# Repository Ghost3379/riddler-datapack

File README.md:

# Enigma Data Pack - Robin: Origins

A functional custom electronic prop for the indie fan film *"Robin: Origins"*. The design is based on the iconic Enigma Data Packs from the Batman *Arkham* universe, engineered as an interactive gadget that can be carried on set and connected to a PC via USB-C to mount as an encrypted data drive.

---

## Hardware Versions

The project contains two distinct hardware designs:

1. **Mini Version (Movie Prop - In Production):** An ultra-compact, stunt-safe, pocket-sized tactical drive (~120 × 65 × 20 mm; PCB: 68 × 50 mm, inspired by rugged portable SSDs like the Samsung T7 Shield). Tailored specifically for the film's action scenes and PC terminal connection.
2. **Full-Size Replica Version:** A heavy, 1:1 scale Arkham military cartridge featuring dual active 40mm cooling fans, internal LiPo battery charging, and full power-rail boost converters.

---

### 1. Mini Version (Movie Hero Prop)
> Located in: [`PCB/Mini Version/Riddler-Datapack mini/`](PCB/Mini%20Version/Riddler-Datapack%20mini/)  
> Full schematic export: [Riddler-Datapack-mini_v1p1.pdf](docs/circuit%20diagrams/Mini/Riddler-Datapack-mini_v1p1.pdf)

Optimized for durability, pocket portability during physical stunt chases, and reliable on-set PC docking:

* **Form Factor:** 4-layer 68 × 50 mm PCB inside a 120 × 65 × 20 mm enclosure with chamfered `PCIe NVMe` base shoe, 7-slot front faceplate grille, and side cooling louvers.
* **Microcontroller:** ESP32-S3-MINI-1 (dual-core, native USB OTG, onboard PCB antenna).
* **Power Architecture:** Purely bus-powered via USB-C (5V VBUS). High-efficiency TLV62568 synchronous step-down buck converter supplies 3.3V @ up to 1A. No internal LiPo batteries required on set, eliminating safety risks and battery downtime.
* **Storage:** MicroSD card socket wired via high-speed **4-bit SDMMC** with hardware pull-ups (4.7kΩ) for fast read/write speeds when mounted as a USB Mass Storage (MSC) drive.
* **Display:** 1.14" IPS TFT LCD (ST7789, 240×135) for crisp "ENIGMA" animations and boot terminals.
* **Illumination:** Integrated addressable RGB LEDs (WS2812B / SK6812) projecting the signature neon green glow through the front casing grille.
* **Protection:** Dedicated USBLC6-2P6 ESD protection on high-speed USB data lines and reverse-polarity Schottky diode on VBUS.

---

### 2. Full-Size Replica Version
> Located in: [`PCB/Riddler-Datapack/`](PCB/Riddler-Datapack/)  
> Full schematic export: [Riddler-Datapack_v0p5.pdf](docs/circuit%20diagrams/Full%20size/Riddler-Datapack_v0p5.pdf)

The full-scale desktop/showcase replica with complete internal subsystem autonomy:

* **Microcontroller:** ESP32-S3-WROOM-1U.
* **Active Cooling:** Dual 40x40mm cooling fans with independent PWM speed control.
* **Power Management:**
  * BQ25170DSGR standalone linear LiPo battery charger (chargeable via USB-C).
  * TPS61023 5V boost converter for fans and high-brightness LED arrays.
  * TLV62568DBV 3.3V buck regulator for MCU logic.
* **Level Shifting:** SN74AHCT125 / 74AHCT1G125 high-speed logic level shifting for 5V LED data lines.
* **Controls:** Physical rocker power switch (`1 / 0`) and dual fan headers.

---

## Visual Reference & In-Game Footage

| Front View (Idle / Off) | Front View (Active "ENIGMA" Display & LEDs) |
| :---: | :---: |
|  |  |

| Top Fans & Lighting | Side Controls & Switch | Bottom Dock ("D-PCK 54") |
| :---: | :---: | :---: |
|  |  |  |

---

## Sources & Credits

* **Concept Art:** [Arkham City Fandom - Enigma Datapack](https://arkhamcity.fandom.com/wiki/Enigma_Datapack?file=Bao-enigma-data-pack.jpg)
* **Video Game Screenshots & Footage:** [Batman Arkham - Enigma Datapacks Gameplay Footage (YouTube)](https://www.youtube.com/watch?v=1w_udK2QxwU)

---

## License
The software/firmware in the `Firmware` directory is licensed under the GNU General Public License v3.0 (GPLv3).

The hardware design files in the `PCB` directory are licensed under the CERN Open Hardware Licence Version 2 - Strongly Reciprocal (CERN-OHL-S).

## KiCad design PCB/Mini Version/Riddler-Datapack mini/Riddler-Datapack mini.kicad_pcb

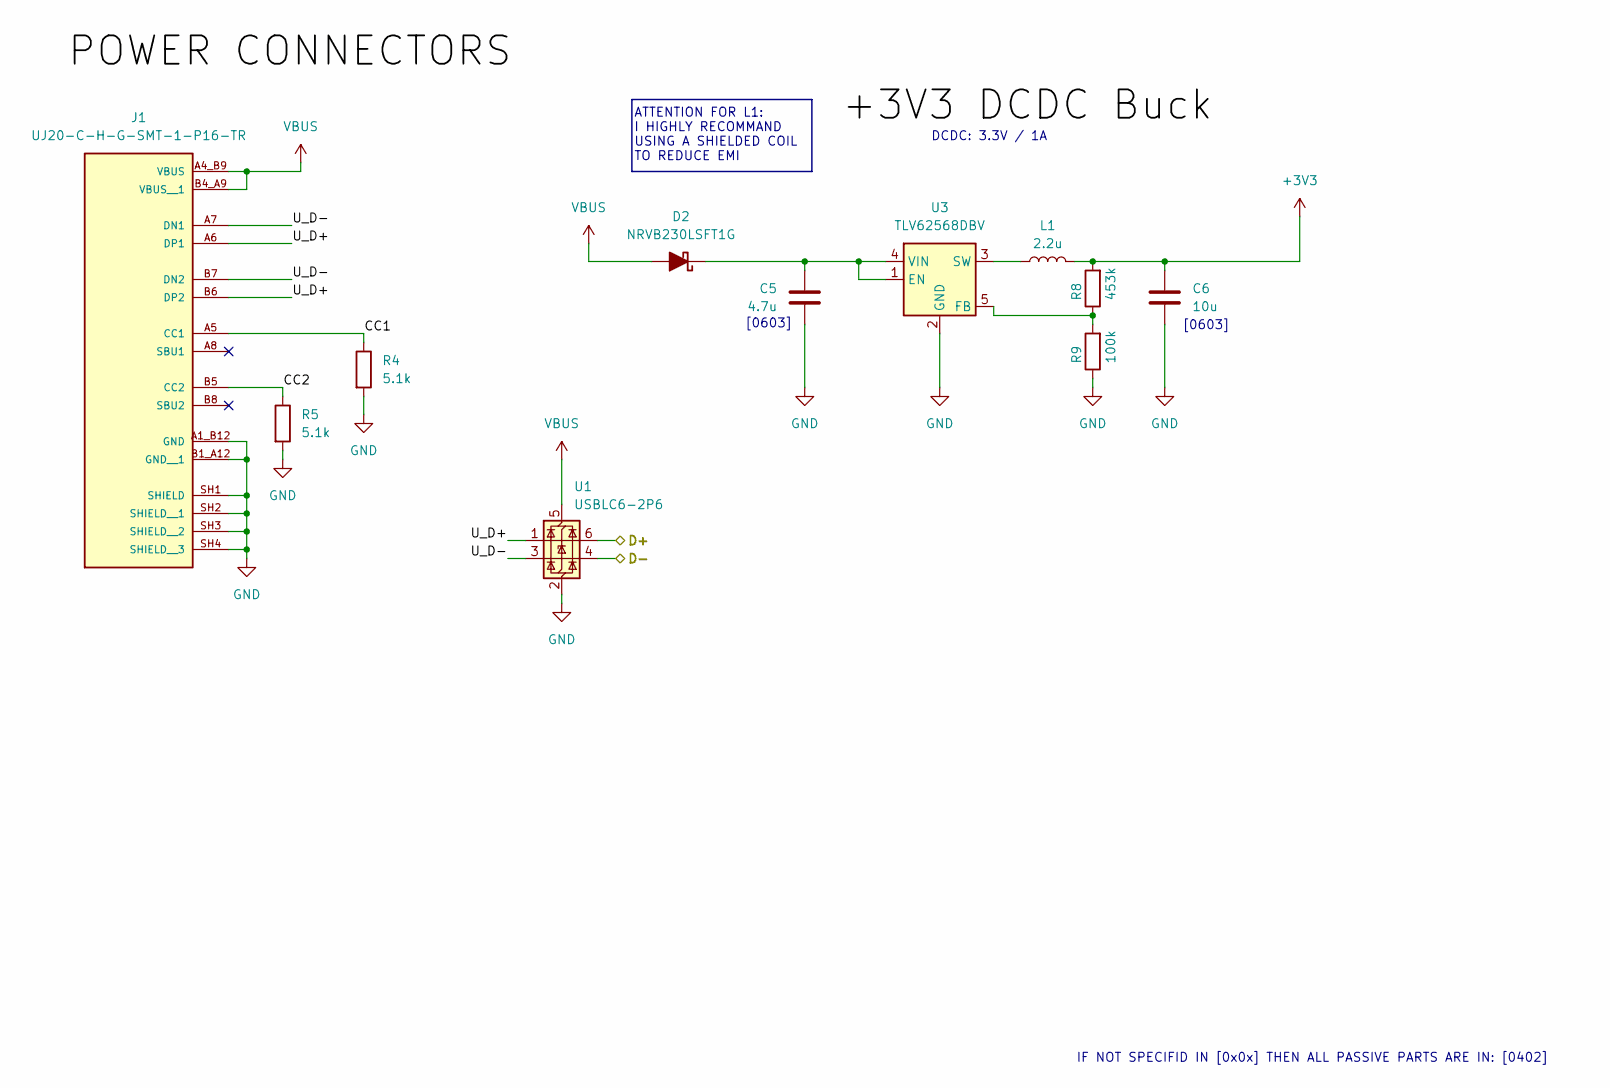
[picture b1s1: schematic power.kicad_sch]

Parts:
C5: 4.7u; C_0603_1608Metric
C6: 10u; C_0603_1608Metric
D2: NRVB230LSFT1G; D_SOD-123
J1: UJ20-C-H-G-SMT-1-P16-TR; SAMESKY_UJ20-C-H-G-SMT-1-P16-TR; PARTREV 1.0
L1: 2.2u; L_1008_2520Metric; Manufacturer part number SRN2510BTA-2R2M
R4, R5: 5.1k; R_0402_1005Metric
R8: 453k; R_0402_1005Metric
R9: 100k; R_0402_1005Metric
U1: USBLC6-2P6; SOT-666
U3: TLV62568DBV; SOT-23-5

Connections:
+3V3: C6.1, L1.2, R8.2; also elsewhere on the board
/Logic/D+: U1.6 (I/O1); also elsewhere on the board
/Logic/D-: U1.4 (I/O2); also elsewhere on the board
/Power/CC1: J1.A5 (CC1), R4.1
/Power/CC2: J1.B5 (CC2), R5.1
/Power/U_D+: J1.A6 (DP1), J1.B6 (DP2), U1.1 (I/O1)
/Power/U_D-: J1.A7 (DN1), J1.B7 (DN2), U1.3 (I/O2)
GND: C5.2, C6.2, J1.A1_B12 (GND), J1.B1_A12 (GND__1), J1.SH1 (SHIELD), J1.SH2 (SHIELD__1), J1.SH3 (SHIELD__2), J1.SH4 (SHIELD__3), R4.2, R5.2, R9.1, U1.2 (GND), U3.2 (GND); also elsewhere on the board
unnamed: C5.1, D2.1 (K), U3.1 (EN), U3.4 (VIN)
unnamed: R8.1, R9.2, U3.5 (FB)
unnamed: L1.1, U3.3 (SW)
VBUS: D2.2 (A), J1.A4_B9 (VBUS), J1.B4_A9 (VBUS__1), U1.5 (VBUS); also elsewhere on the board

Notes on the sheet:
[0603]
ATTENTION FOR L1: I HIGHLY RECOMMAND USING A SHIELDED COIL TO REDUCE EMI
DCDC: 3.3V / 1A
IF NOT SPECIFID IN [0x0x] THEN ALL PASSIVE PARTS ARE IN: [0402]

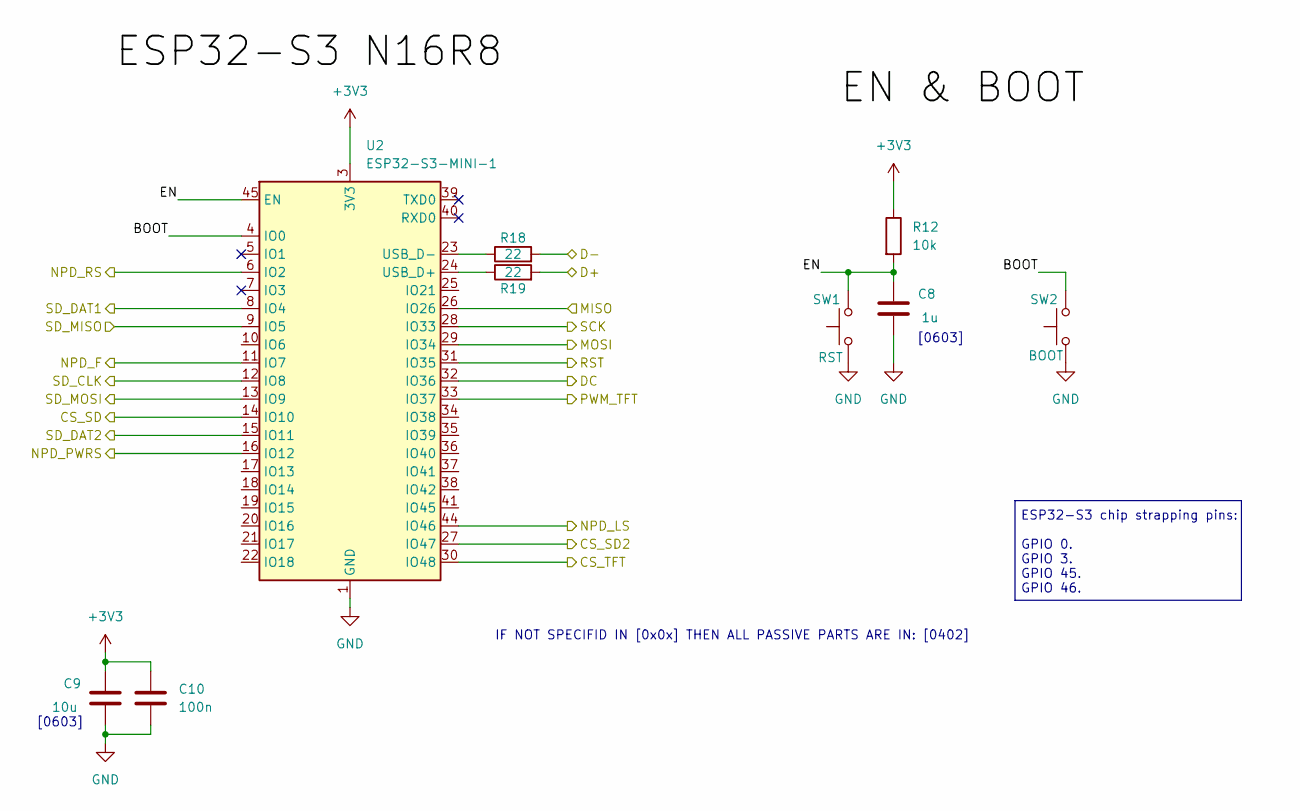
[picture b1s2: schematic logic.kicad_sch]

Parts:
C8: 1u; C_0603_1608Metric
C9: 10u; C_0603_1608Metric
C10: 100n; C_0402_1005Metric
R12: 10k; R_0402_1005Metric
R18, R19: 22; R_0402_1005Metric
SW1: RST; SW_SPST_PTS810
SW2: BOOT; SW_SPST_PTS810
U2: ESP32-S3-MINI-1; ESP32-S2-MINI-1

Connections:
+3V3: C9.1, C10.1, R12.1, U2.3 (3V3); also elsewhere on the board
/Logic/BOOT: SW2.2, U2.4 (IO0)
/Logic/CS_SD: U2.14 (IO10); also elsewhere on the board
/Logic/CS_SD2: U2.27 (IO47); also elsewhere on the board
/Logic/CS_TFT: U2.30 (IO48); also elsewhere on the board
/Logic/D+: R19.2; also elsewhere on the board
/Logic/D-: R18.2; also elsewhere on the board
/Logic/DC: U2.32 (IO36); also elsewhere on the board
/Logic/EN: C8.1, R12.2, SW1.2, U2.45 (EN)
/Logic/MISO: U2.26 (IO26); also elsewhere on the board
/Logic/MOSI: U2.29 (IO34); also elsewhere on the board
/Logic/NPD_F: U2.11 (IO7); also elsewhere on the board
/Logic/NPD_LS: U2.44 (IO46); also elsewhere on the board
/Logic/NPD_PWRS: U2.16 (IO12); also elsewhere on the board
/Logic/NPD_RS: U2.6 (IO2); also elsewhere on the board
/Logic/PWM_TFT: U2.33 (IO37); also elsewhere on the board
/Logic/RST: U2.31 (IO35); also elsewhere on the board
/Logic/SCK: U2.28 (IO33); also elsewhere on the board
/Logic/SD_CLK: U2.12 (IO8); also elsewhere on the board
/Logic/SD_DAT1: U2.8 (IO4); also elsewhere on the board
/Logic/SD_DAT2: U2.15 (IO11); also elsewhere on the board
/Logic/SD_MISO: U2.9 (IO5); also elsewhere on the board
/Logic/SD_MOSI: U2.13 (IO9); also elsewhere on the board
GND: C8.2, C9.2, C10.2, SW1.1, SW2.1, U2.1 (GND), U2.2 (GND), U2.42 (GND), U2.43 (GND), U2.46 (GND), U2.47 (GND), U2.48 (GND), U2.49 (GND), U2.50 (GND), U2.51 (GND), U2.52 (GND), U2.53 (GND), U2.54 (GND), U2.55 (GND), U2.56 (GND), U2.57 (GND), U2.58 (GND), U2.59 (GND), U2.60 (GND), U2.61 (GND), U2.62 (GND), U2.63 (GND), U2.64 (GND), U2.65 (GND); also elsewhere on the board
unnamed: R19.1, U2.24 (USB_D+)
unnamed: R18.1, U2.23 (USB_D-)

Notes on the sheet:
IF NOT SPECIFID IN [0x0x] THEN ALL PASSIVE PARTS ARE IN: [0402]
ESP32-S3 chip strapping pins: GPIO 0. GPIO 3. GPIO 45. GPIO 46.
[0603]

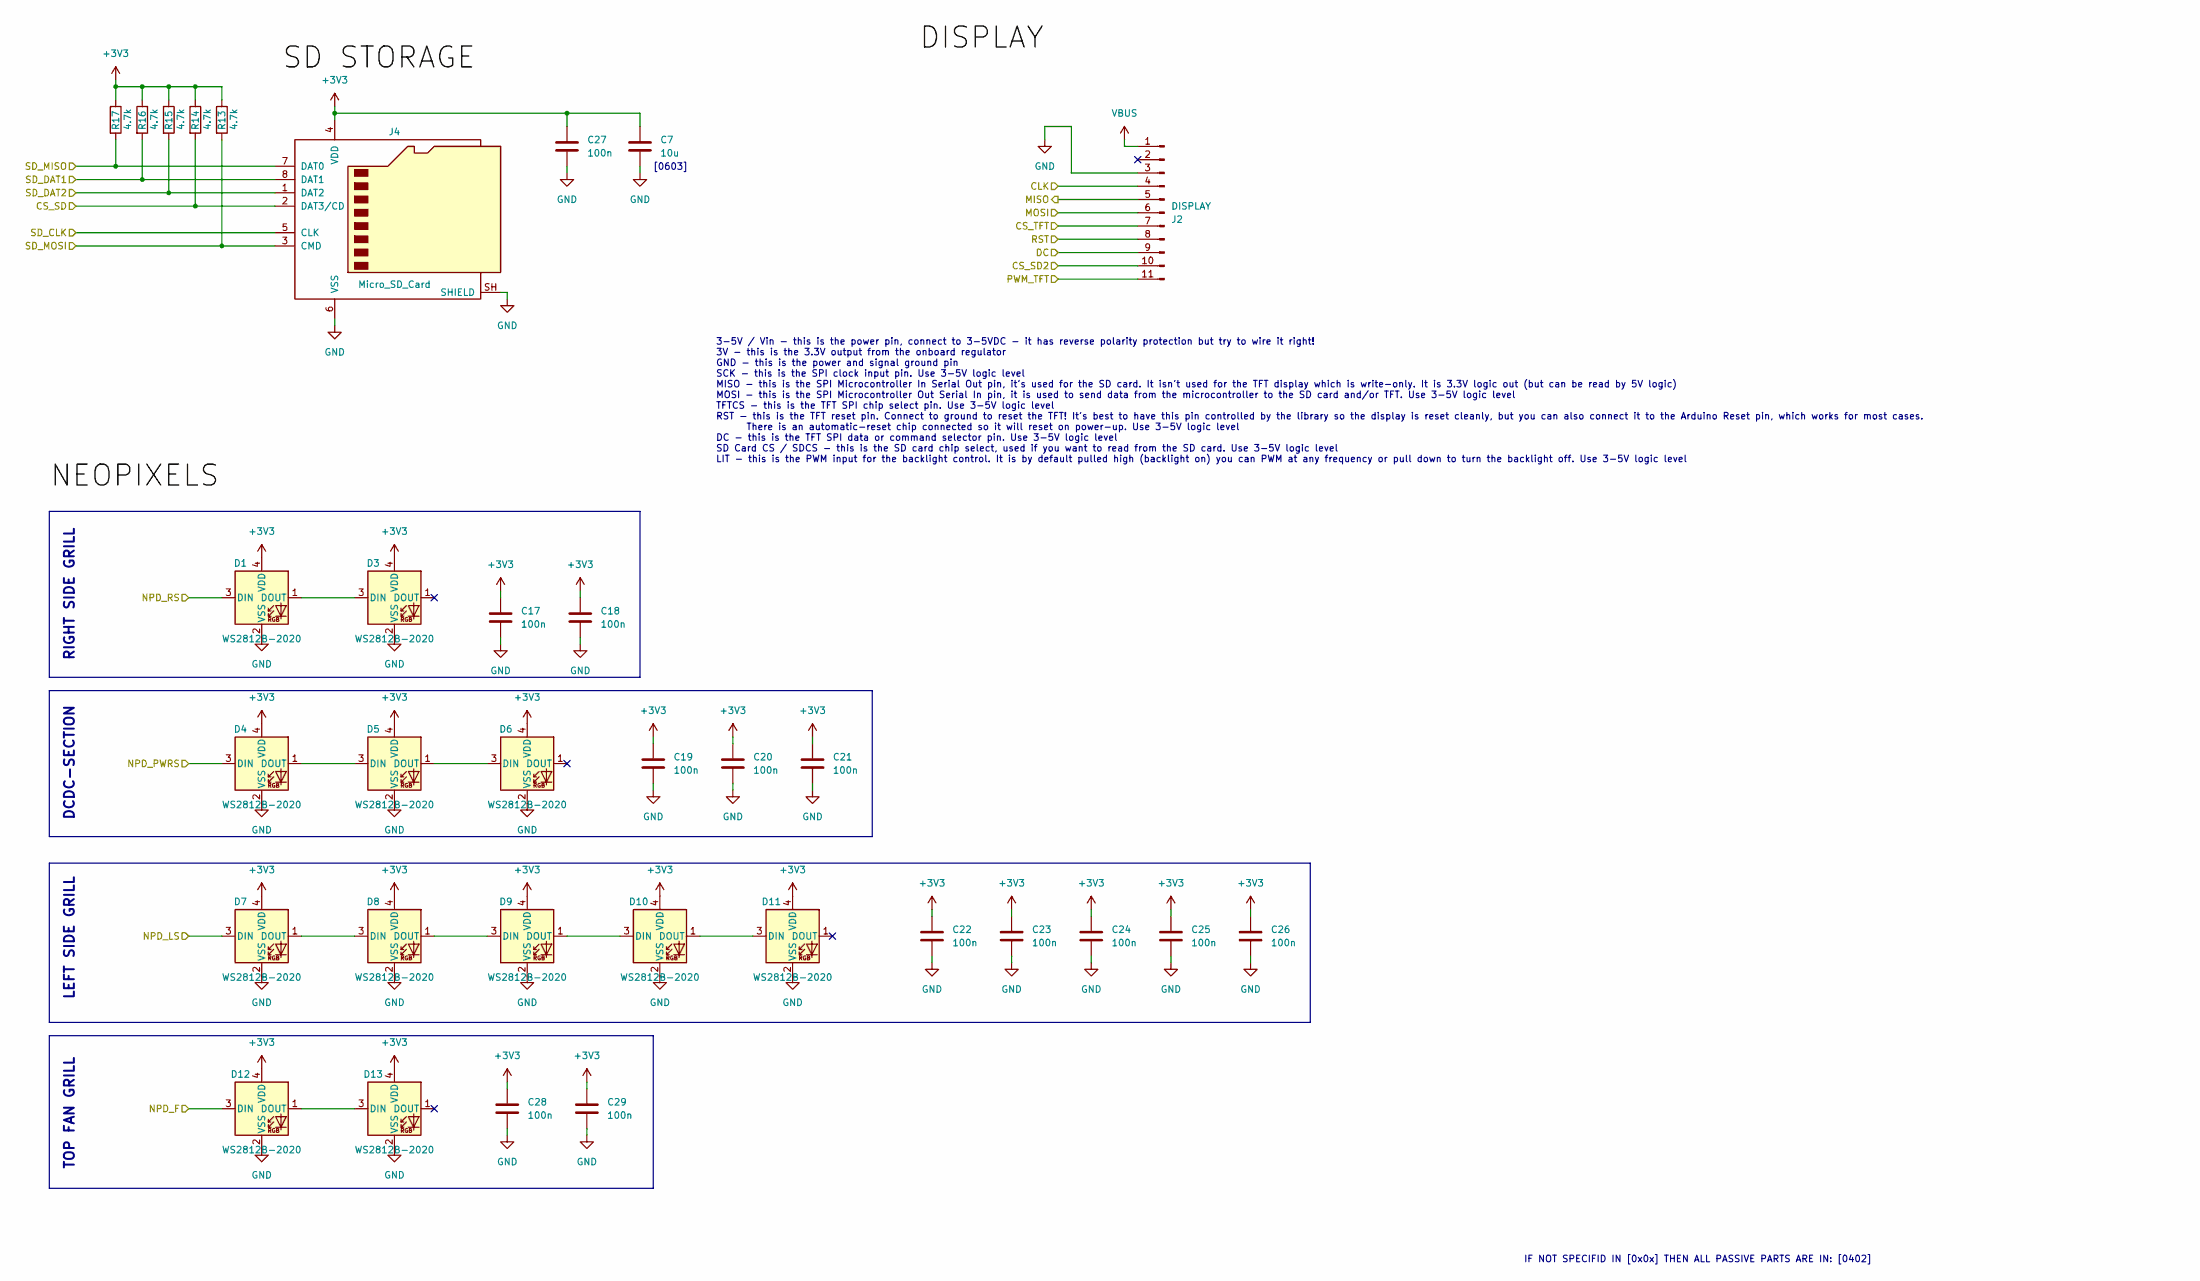
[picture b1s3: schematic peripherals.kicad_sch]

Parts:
C7: 10u; C_0603_1608Metric
C17, C18, C19, C20, C21, C22, C23, C24, C25, C26, C27, C28, C29: 100n; C_0402_1005Metric
D1, D3, D4, D5, D6, D7, D8, D9, D10, D11, D12, D13: WS2812B-2020; LED_WS2812B-2020_PLCC4_2.0x2.0mm
J2: DISPLAY; PinHeader_1x11_P2.54mm_Vertical
J4: Micro_SD_Card; microSD_HC_Wuerth_693072010801
R13, R14, R15, R16, R17: 4.7k; R_0402_1005Metric

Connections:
+3V3: C7.1, C17.1, C18.1, C19.1, C20.1, C21.1, C22.1, C23.1, C24.1, C25.1, C26.1, C27.1, C28.1, C29.1, D1.4 (VDD), D3.4 (VDD), D4.4 (VDD), D5.4 (VDD), D6.4 (VDD), D7.4 (VDD), D8.4 (VDD), D9.4 (VDD), D10.4 (VDD), D11.4 (VDD), D12.4 (VDD), D13.4 (VDD), J4.4 (VDD), R13.1, R14.1, R15.1, R16.1, R17.1; also elsewhere on the board
/Logic/CS_SD: J4.2 (DAT3/CD), R14.2; also elsewhere on the board
/Logic/CS_SD2: J2.10; also elsewhere on the board
/Logic/CS_TFT: J2.7; also elsewhere on the board
/Logic/DC: J2.9; also elsewhere on the board
/Logic/MISO: J2.5; also elsewhere on the board
/Logic/MOSI: J2.6; also elsewhere on the board
/Logic/NPD_F: D12.3 (DIN); also elsewhere on the board
/Logic/NPD_LS: D7.3 (DIN); also elsewhere on the board
/Logic/NPD_PWRS: D4.3 (DIN); also elsewhere on the board
/Logic/NPD_RS: D1.3 (DIN); also elsewhere on the board
/Logic/PWM_TFT: J2.11; also elsewhere on the board
/Logic/RST: J2.8; also elsewhere on the board
/Logic/SCK: J2.4; also elsewhere on the board
/Logic/SD_CLK: J4.5 (CLK); also elsewhere on the board
/Logic/SD_DAT1: J4.8 (DAT1), R16.2; also elsewhere on the board
/Logic/SD_DAT2: J4.1 (DAT2), R15.2; also elsewhere on the board
/Logic/SD_MISO: J4.7 (DAT0), R17.2; also elsewhere on the board
/Logic/SD_MOSI: J4.3 (CMD), R13.2; also elsewhere on the board
GND: C7.2, C17.2, C18.2, C19.2, C20.2, C21.2, C22.2, C23.2, C24.2, C25.2, C26.2, C27.2, C28.2, C29.2, D1.2 (VSS), D3.2 (VSS), D4.2 (VSS), D5.2 (VSS), D6.2 (VSS), D7.2 (VSS), D8.2 (VSS), D9.2 (VSS), D10.2 (VSS), D11.2 (VSS), D12.2 (VSS), D13.2 (VSS), J2.3, J4.6 (VSS), J4.SH (SHIELD); also elsewhere on the board
unnamed: D1.1 (DOUT), D3.3 (DIN)
unnamed: D4.1 (DOUT), D5.3 (DIN)
unnamed: D5.1 (DOUT), D6.3 (DIN)
unnamed: D7.1 (DOUT), D8.3 (DIN)
unnamed: D8.1 (DOUT), D9.3 (DIN)
unnamed: D9.1 (DOUT), D10.3 (DIN)
unnamed: D10.1 (DOUT), D11.3 (DIN)
unnamed: D12.1 (DOUT), D13.3 (DIN)
VBUS: J2.1; also elsewhere on the board

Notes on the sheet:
IF NOT SPECIFID IN [0x0x] THEN ALL PASSIVE PARTS ARE IN: [0402]
TOP FAN GRILL
[0603]
DCDC-SECTION
LEFT SIDE GRILL
3-5V / Vin - this is the power pin, connect to 3-5VDC - it has reverse polarity protection but try to wire it right! 3V - this is the 3.3V output from the onboard regulator GND - this is the power and signal ground pin SCK - this is the SPI clock input pin. Use 3-5V logic level MISO - this is the S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
RIGHT SIDE GRILL

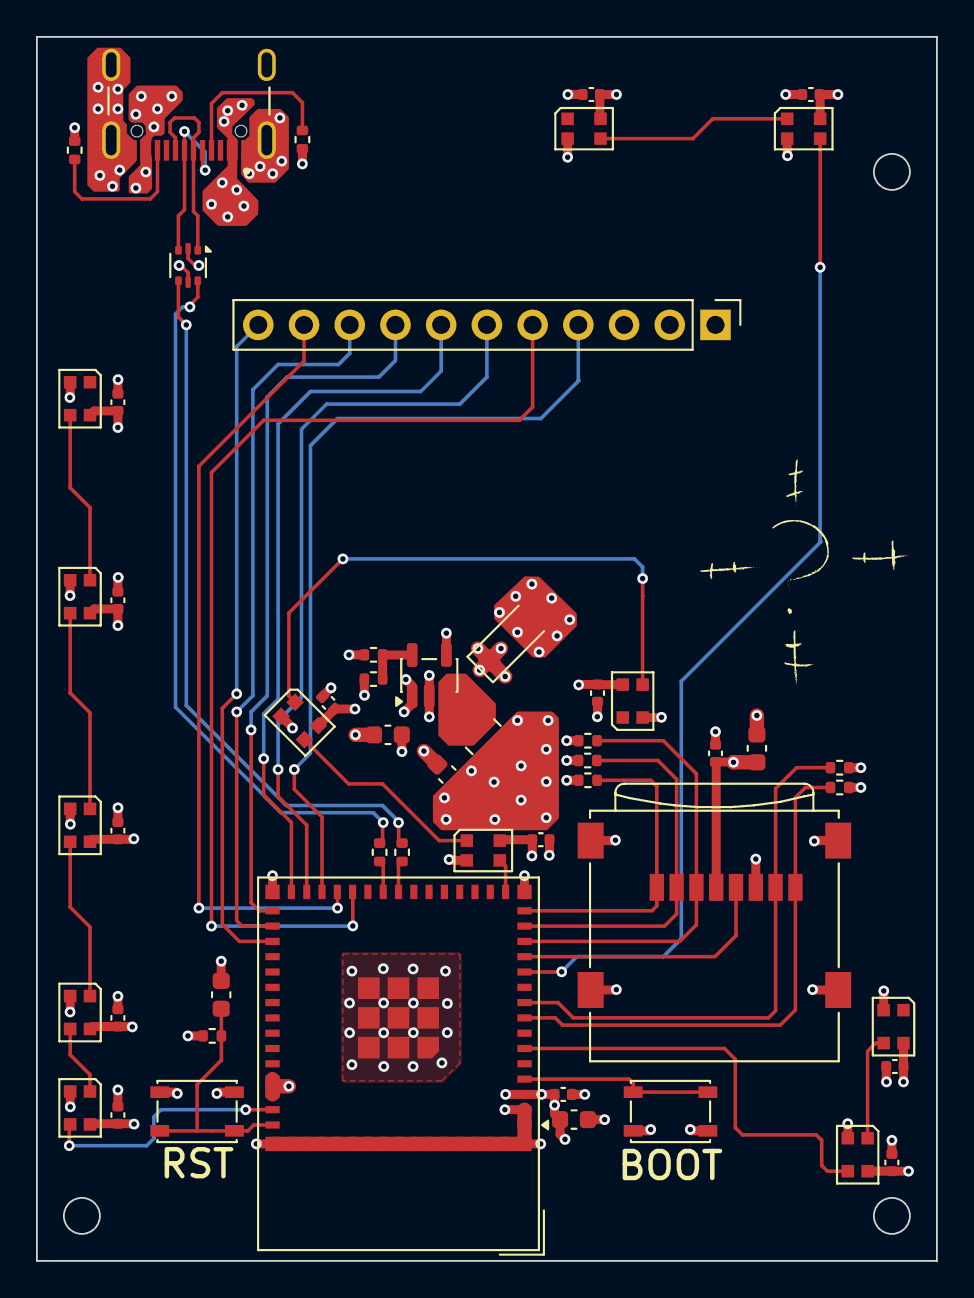
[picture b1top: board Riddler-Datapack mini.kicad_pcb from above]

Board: 4 copper layers, 50.0 x 68.0 mm, 53 parts (0 on the bottom side), 42 nets.

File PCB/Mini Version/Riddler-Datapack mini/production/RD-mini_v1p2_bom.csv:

Designator,Footprint,Quantity,Value,LCSC Part #
"C10, C17, C18, C19, C20, C21, C22, C23, C24, C25, C26, C27, C28, C29",0402,14,100n,
C5,0603,1,4.7u,
"C6, C7, C9",0603,3,10u,
C8,0603,1,1u,
"D1, D10, D11, D12, D13, D3, D4, D5, D6, D7, D8, D9",LED_WS2812B-2020_PLCC4_2.0x2.0mm,12,WS2812B-2020,
D2,D_SOD-123,1,NRVB230LSFT1G,
J1,SAMESKY_UJ20-C-H-G-SMT-1-P16-TR,1,UJ20-C-H-G-SMT-1-P16-TR,
J2,PinHeader_1x11_P2.54mm_Vertical,1,DISPLAY,
J4,microSD_HC_Wuerth_693072010801,1,Micro_SD_Card,
L1,1008,1,2.2u,
R12,0402,1,10k,
"R13, R14, R15, R16, R17",0402,5,4.7k,
"R18, R19",0402,2,22,
"R4, R5",0402,2,5.1k,
R8,0402,1,453k,
R9,0402,1,100k,
SW1,SW_SPST_PTS810,1,RST,
SW2,SW_SPST_PTS810,1,BOOT,
U1,SOT-666,1,USBLC6-2P6,
U2,ESP32-S2-MINI-1,1,ESP32-S3-MINI-1,
U3,SOT-23-5,1,TLV62568DBV,

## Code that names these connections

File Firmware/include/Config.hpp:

#pragma once

#include <Arduino.h>

// ==============================================================================
// HARDWARE PIN ASSIGNMENTS (Mini Version v1.2)
// Matches KiCad layout in PCB/Mini Version/Riddler-Datapack mini/
// ==============================================================================

// --- ST7789 1.14" IPS TFT LCD (240x135 SPI) ---
#define PIN_TFT_SCLK      33
#define PIN_TFT_MOSI      34
#define PIN_TFT_MISO      26
#define PIN_TFT_CS        48
#define PIN_TFT_DC        36
#define PIN_TFT_RST       35
#define PIN_TFT_BL        37    // Backlight PWM

#define TFT_WIDTH         240
#define TFT_HEIGHT        135

// --- MicroSD Card Slot (4-bit SDMMC Interface) ---
#define PIN_SD_CLK        8
#define PIN_SD_CMD        9     // MOSI
#define PIN_SD_D0         5     // MISO
#define PIN_SD_D1         4
#define PIN_SD_D2         11
#define PIN_SD_D3         10    // CS
#define PIN_SD_CS2        47

// --- Addressable WS2812B-2020 LEDs (12 LEDs across 4 channels) ---
#define PIN_LED_FRONT     7     // NPD_F    (2 LEDs: D12, D13 - Front Grille)
#define NUM_LEDS_FRONT    2

#define PIN_LED_RIGHT     2     // NPD_RS   (2 LEDs: D1, D3 - Right Louvers)
#define NUM_LEDS_RIGHT    2

#define PIN_LED_LEFT      46    // NPD_LS   (5 LEDs: D7..D11 - Left Louvers)
#define NUM_LEDS_LEFT     5

#define PIN_LED_REAR      12    // NPD_PWRS (3 LEDs: D4..D6 - Faux Fan / Rear)
#define NUM_LEDS_REAR     3

#define NUM_LEDS_TOTAL    (NUM_LEDS_FRONT + NUM_LEDS_RIGHT + NUM_LEDS_LEFT + NUM_LEDS_REAR)

// --- Actor & Control Buttons ---
#define PIN_BTN_BOOT      0     // SW2 (Boot / Multi-gesture trigger)

// --- USB Identifiers ---
#define USB_VENDOR_ID     "GOTHAM"
#define USB_PRODUCT_ID    "ENIGMA"
#define USB_REVISION      "1.0"
#define USB_VOLUME_LABEL  "ENIGMA"

// ==============================================================================
// CONFIGURATION DEFAULTS
// ==============================================================================
struct PropConfig {
    uint8_t  display_brightness = 85;       // 10 - 100%
    uint8_t  led_brightness     = 38;       // 15% brightness (0 - 255)
    uint8_t  ticker_speed       = 2;        // 1 (slow) to 8 (fast)
    float    quote_delay_min    = 1.5f;     // Minimum pause between quotes in seconds (e.g. 0.5s or random(5,10))
    float    quote_delay_max    = 1.5f;     // Maximum pause between quotes in seconds
    uint8_t  ambient_hue        = 96;       // 96 = Arkham Emerald Green (0-255 HSV)
    uint8_t  pulse_speed        = 14;       // Beats per minute for idle breath
    bool     show_waveform      = true;     // Show dynamic Arkham oscilloscope
    bool     flicker_on_io      = true;     // Smooth ripple on disk read/write
};
